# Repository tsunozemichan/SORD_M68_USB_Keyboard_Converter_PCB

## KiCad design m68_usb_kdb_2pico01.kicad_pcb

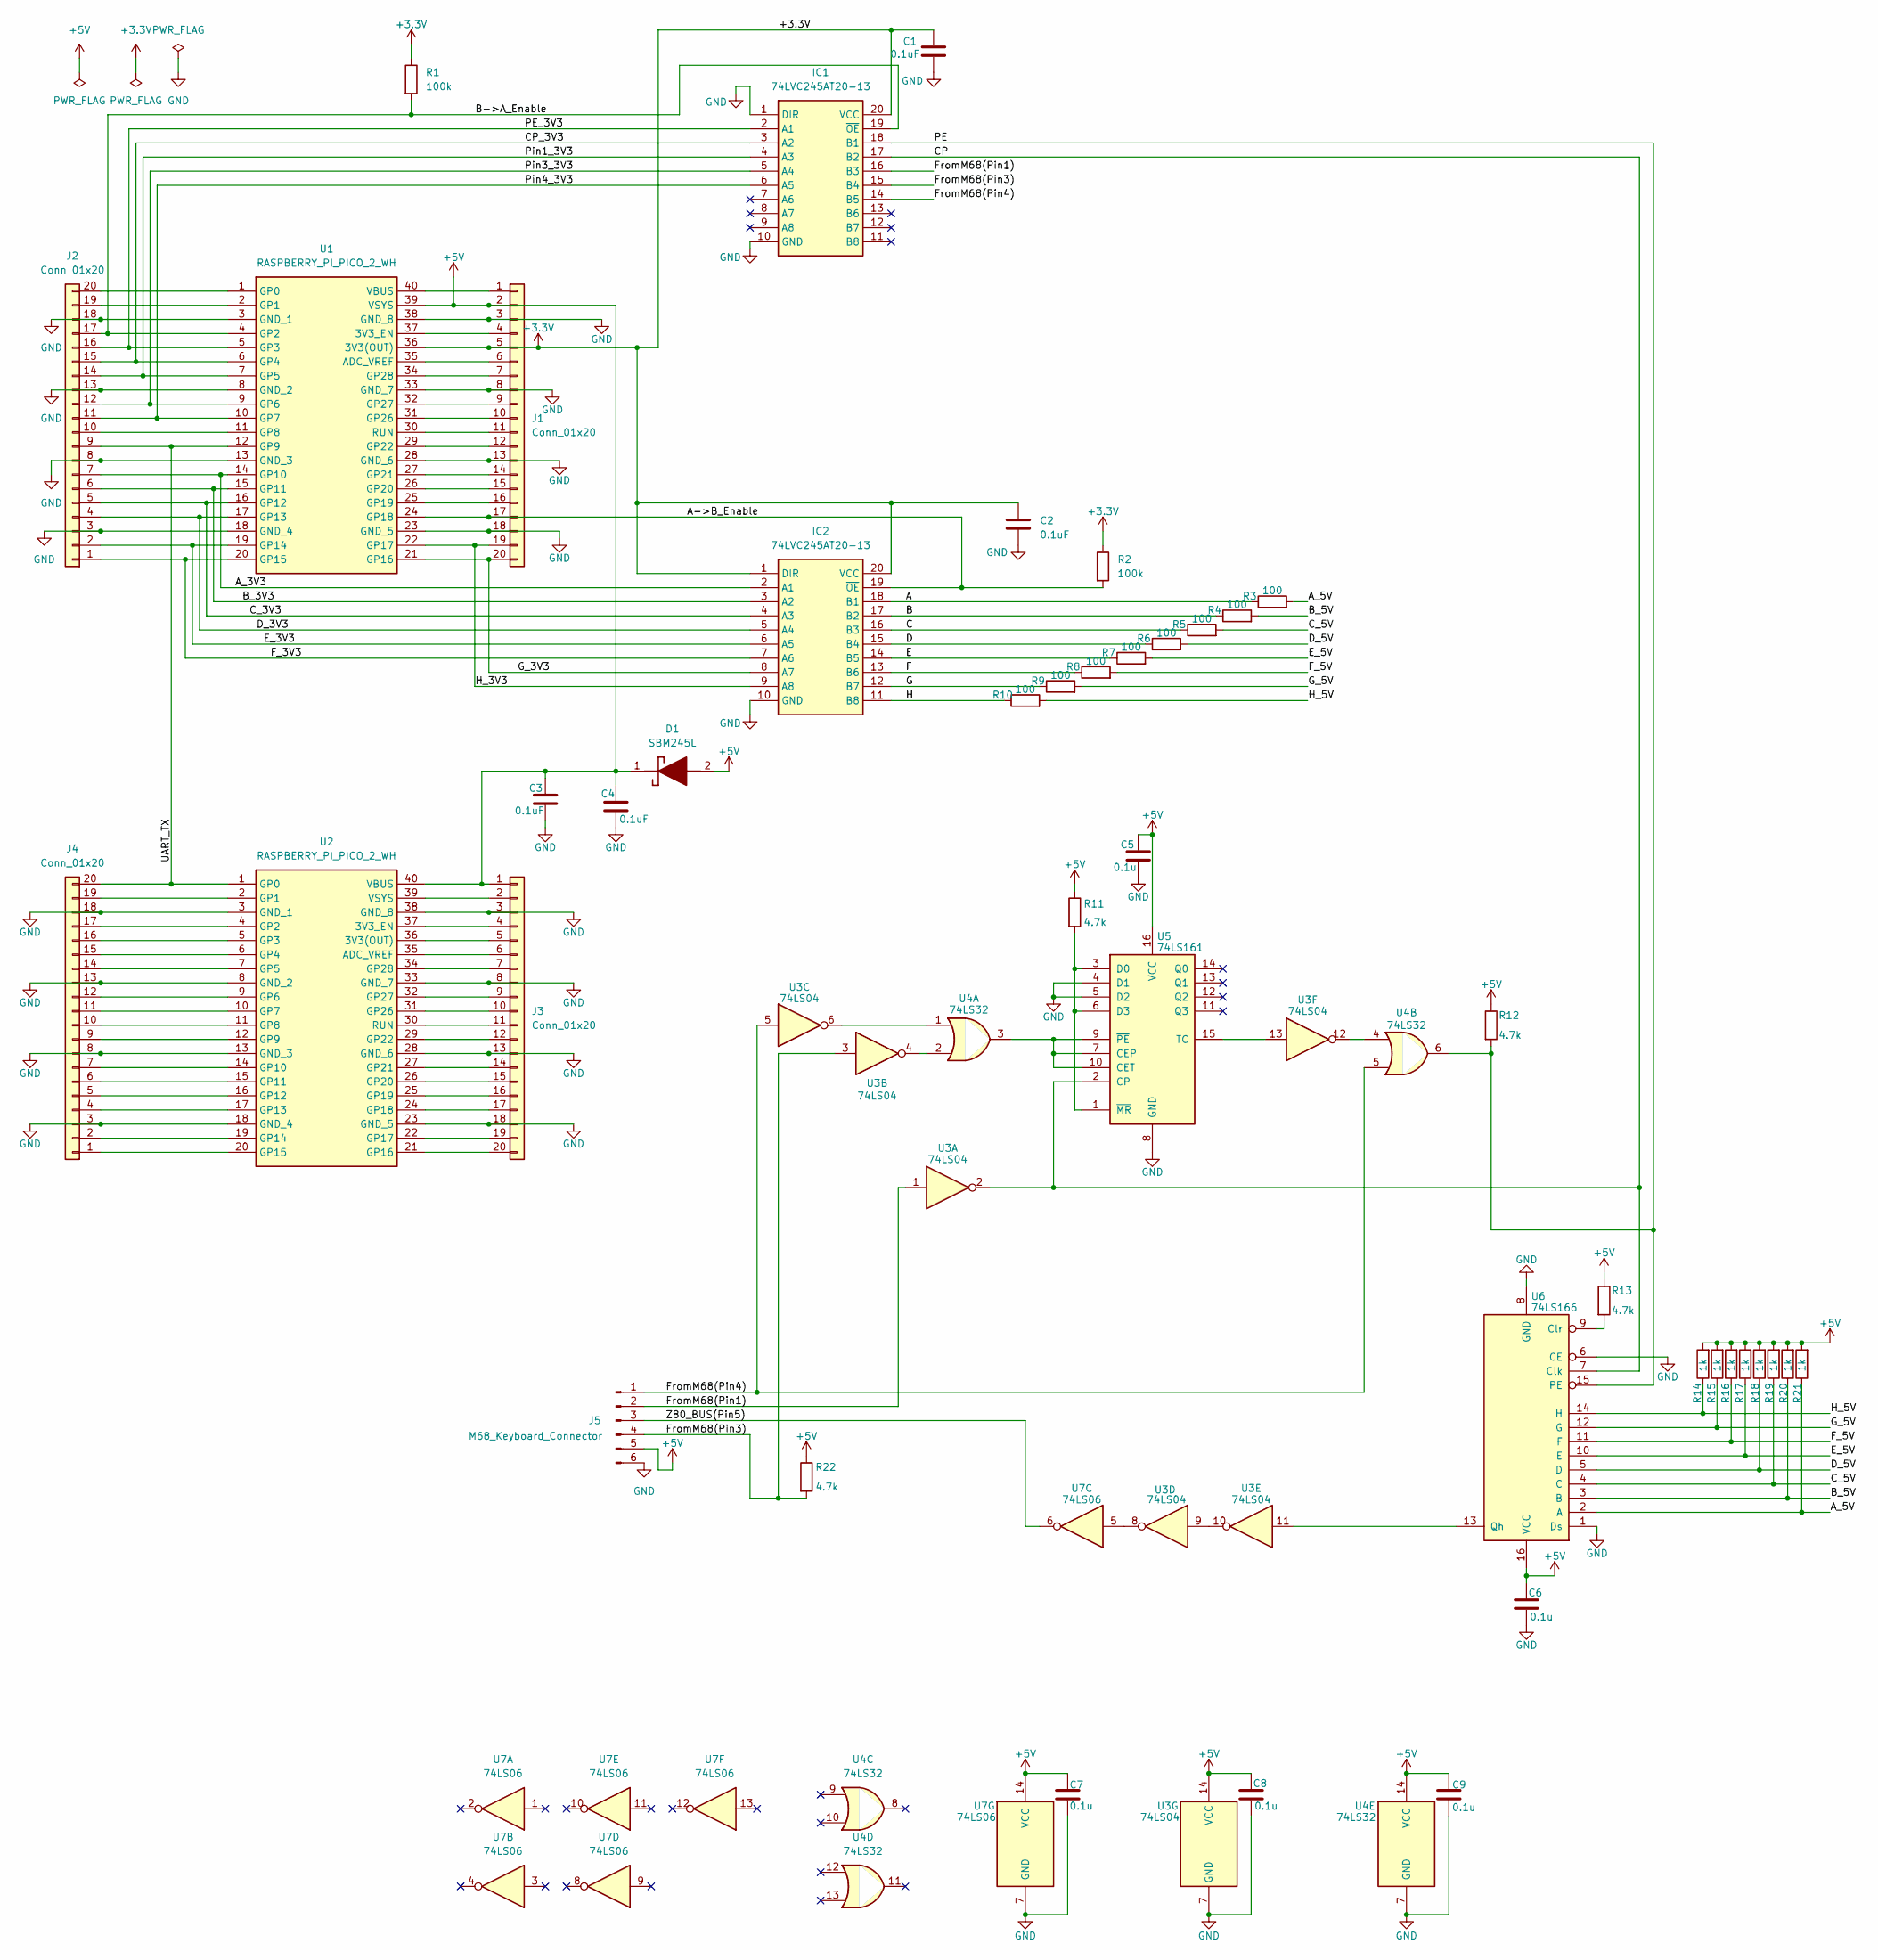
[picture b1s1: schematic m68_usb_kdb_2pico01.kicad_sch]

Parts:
C1, C2, C3, C4: 0.1uF; C_Disc_D3.0mm_W1.6mm_P2.50mm
C5, C6, C7, C8, C9: 0.1u; C_Disc_D5.0mm_W2.5mm_P2.50mm
D1: SBM245L; DIOAD1405W86L465D235; Manufacturer_Part_Number SBM245L
IC1, IC2: 74LVC245AT20-13; SOP65P640X120-20N; Manufacturer_Part_Number 74LVC245AT20-13; Mouser Part Number 621-74LVC245AT20-13
J1, J2, J3, J4: Conn_01x20; PinSocket_1x20_P2.54mm_Vertical
J5: M68_Keyboard_Connector; JST_XH_S6B-XH-A_1x06_P2.50mm_Horizontal
R1, R2: 100k; R_Axial_DIN0207_L6.3mm_D2.5mm_P10.16mm_Horizontal
R3, R4, R5, R6, R7, R8, R9, R10: 100; R_Axial_DIN0207_L6.3mm_D2.5mm_P10.16mm_Horizontal
R11, R12, R13, R22: 4.7k; R_Axial_DIN0207_L6.3mm_D2.5mm_P10.16mm_Horizontal
R14, R15, R16, R17, R18, R19, R20, R21: 1k; R_Axial_DIN0207_L6.3mm_D2.5mm_P10.16mm_Horizontal
U1, U2: RASPBERRY_PI_PICO_2_WH; RASPBERRYPIPICO2WH; Manufacturer_Part_Number RASPBERRY PI PICO 2 WH
U3: 74LS04; DIP-14_W7.62mm_Socket_LongPads
U4: 74LS32; DIP-14_W7.62mm_Socket_LongPads
U5: 74LS161; DIP-16_W7.62mm_Socket_LongPads
U6: 74LS166; DIP-16_W7.62mm_Socket_LongPads
U7: 74LS06; DIP-14_W7.62mm_Socket_LongPads

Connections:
+3.3V: C1.1, C2.1, IC1.20 (VCC), IC2.1 (DIR), IC2.20 (VCC), J1.5, R1.1, R2.1, U1.36 (3V3(OUT))
+5V: C3.1, C4.1, C5.1, C6.1, C7.1, C8.1, C9.1, D1.1 (K), D1.2 (A), J1.2, J3.1, J5.5, R11.1, R12.1, R13.1, R14.2, R15.2, R16.2, R17.2, R18.2, R19.2, R20.2, R21.2, R22.1, U1.39 (VSYS), U2.40 (VBUS), U3.14 (VCC), U4.14 (VCC), U5.16 (VCC), U6.16 (VCC), U7.14 (VCC)
/A: IC2.18 (B1), R3.1
/A->B_Enable: IC2.19 (~OE), J1.17, R2.2, U1.24 (GP18)
/A_3V3: IC2.2 (A1), J2.7, U1.14 (GP10)
/A_5V: R3.2, R21.1, U6.2 (A)
/B: IC2.17 (B2), R4.1
/B->A_Enable: IC1.19 (~OE), J2.17, R1.2, U1.4 (GP2)
/B_3V3: IC2.3 (A2), J2.6, U1.15 (GP11)
/B_5V: R4.2, R20.1, U6.3 (B)
/C: IC2.16 (B3), R5.1
/CP: IC1.17 (B2), U3.2, U5.2 (CP), U6.7 (Clk)
/CP_3V3: IC1.3 (A2), J2.15, U1.6 (GP4)
/C_3V3: IC2.4 (A3), J2.5, U1.16 (GP12)
/C_5V: R5.2, R19.1, U6.4 (C)
/D: IC2.15 (B4), R6.1
/D_3V3: IC2.5 (A4), J2.4, U1.17 (GP13)
/D_5V: R6.2, R18.1, U6.5 (D)
/E: IC2.14 (B5), R7.1
/E_3V3: IC2.6 (A5), J2.2, U1.19 (GP14)
/E_5V: R7.2, R17.1, U6.10 (E)
/F: IC2.13 (B6), R8.1
/F_3V3: IC2.7 (A6), J2.1, U1.20 (GP15)
/F_5V: R8.2, R16.1, U6.11 (F)
/FromM68(Pin1): IC1.16 (B3), J5.2, U3.1
/FromM68(Pin3): IC1.15 (B4), J5.4, R22.2, U3.3
/FromM68(Pin4): IC1.14 (B5), J5.1, U3.5, U4.5
/G: IC2.12 (B7), R9.1
/G_3V3: IC2.8 (A7), J1.20, U1.21 (GP16)
/G_5V: R9.2, R15.1, U6.12 (G)
/H: IC2.11 (B8), R10.1
/H_3V3: IC2.9 (A8), J1.19, U1.22 (GP17)
/H_5V: R10.2, R14.1, U6.14 (H)
/PE: IC1.18 (B1), R12.2, U4.6, U6.15 (PE)
/PE_3V3: IC1.2 (A1), J2.16, U1.5 (GP3)
/Pin1_3V3: IC1.4 (A3), J2.14, U1.7 (GP5)
/Pin3_3V3: IC1.5 (A4), J2.12, U1.9 (GP6)
/Pin4_3V3: IC1.6 (A5), J2.11, U1.10 (GP7)
/UART_TX: J2.9, J4.20, U1.12 (GP9), U2.1 (GP0)
/Z80_BUS(Pin5): J5.3, U7.6
GND: C1.2, C2.2, C3.2, C4.2, C5.2, C6.2, C7.2, C8.2, C9.2, IC1.1 (DIR), IC1.10 (GND), IC2.10 (GND), J1.3, J1.8, J1.13, J1.18, J2.3, J2.8, J2.13, J2.18, J3.3, J3.8, J3.13, J3.18, J4.3, J4.8, J4.13, J4.18, J5.6, U1.3 (GND_1), U1.8 (GND_2), U1.13 (GND_3), U1.18 (GND_4), U1.23 (GND_5), U1.28 (GND_6), U1.33 (GND_7), U1.38 (GND_8), U2.3 (GND_1), U2.8 (GND_2), U2.13 (GND_3), U2.18 (GND_4), U2.23 (GND_5), U2.28 (GND_6), U2.33 (GND_7), U2.38 (GND_8), U3.7 (GND), U4.7 (GND), U5.4 (D1), U5.5 (D2), U5.8 (GND), U6.1 (Ds), U6.6 (CE), U6.8 (GND), U7.7 (GND)
unnamed: J1.1, U1.40 (VBUS)
unnamed: J1.4, U1.37 (3V3_EN)
unnamed: J1.6, U1.35 (ADC_VREF)
unnamed: J1.7, U1.34 (GP28)
unnamed: J1.9, U1.32 (GP27)
unnamed: J1.10, U1.31 (GP26)
unnamed: J1.11, U1.30 (RUN)
unnamed: J1.12, U1.29 (GP22)
unnamed: J1.14, U1.27 (GP21)
unnamed: J1.15, U1.26 (GP20)
unnamed: J1.16, U1.25 (GP19)
unnamed: J2.10, U1.11 (GP8)
unnamed: J2.19, U1.2 (GP1)
unnamed: J2.20, U1.1 (GP0)
unnamed: J3.2, U2.39 (VSYS)
unnamed: J3.4, U2.37 (3V3_EN)
unnamed: J3.5, U2.36 (3V3(OUT))
unnamed: J3.6, U2.35 (ADC_VREF)
unnamed: J3.7, U2.34 (GP28)
unnamed: J3.9, U2.32 (GP27)
unnamed: J3.10, U2.31 (GP26)
unnamed: J3.11, U2.30 (RUN)
unnamed: J3.12, U2.29 (GP22)
unnamed: J3.14, U2.27 (GP21)
unnamed: J3.15, U2.26 (GP20)
unnamed: J3.16, U2.25 (GP19)
unnamed: J3.17, U2.24 (GP18)
unnamed: J3.19, U2.22 (GP17)
unnamed: J3.20, U2.21 (GP16)
unnamed: J4.1, U2.20 (GP15)
unnamed: J4.2, U2.19 (GP14)
unnamed: J4.4, U2.17 (GP13)
unnamed: J4.5, U2.16 (GP12)
unnamed: J4.6, U2.15 (GP11)
unnamed: J4.7, U2.14 (GP10)
unnamed: J4.9, U2.12 (GP9)
unnamed: J4.10, U2.11 (GP8)
unnamed: J4.11, U2.10 (GP7)
unnamed: J4.12, U2.9 (GP6)
unnamed: J4.14, U2.7 (GP5)
unnamed: J4.15, U2.6 (GP4)
unnamed: J4.16, U2.5 (GP3)
unnamed: J4.17, U2.4 (GP2)
unnamed: J4.19, U2.2 (GP1)
unnamed: U3.4, U4.2
unnamed: U3.6, U4.1
unnamed: U3.8, U7.5
unnamed: U3.9, U3.10
unnamed: U3.12, U4.4
unnamed: U4.3, U5.7 (CEP), U5.9 (~PE), U5.10 (CET)
unnamed: R11.2, U5.1 (~MR), U5.3 (D0), U5.6 (D3)
unnamed: U3.13, U5.15 (TC)
unnamed: R13.2, U6.9 (Clr)
unnamed: U3.11, U6.13 (Qh)

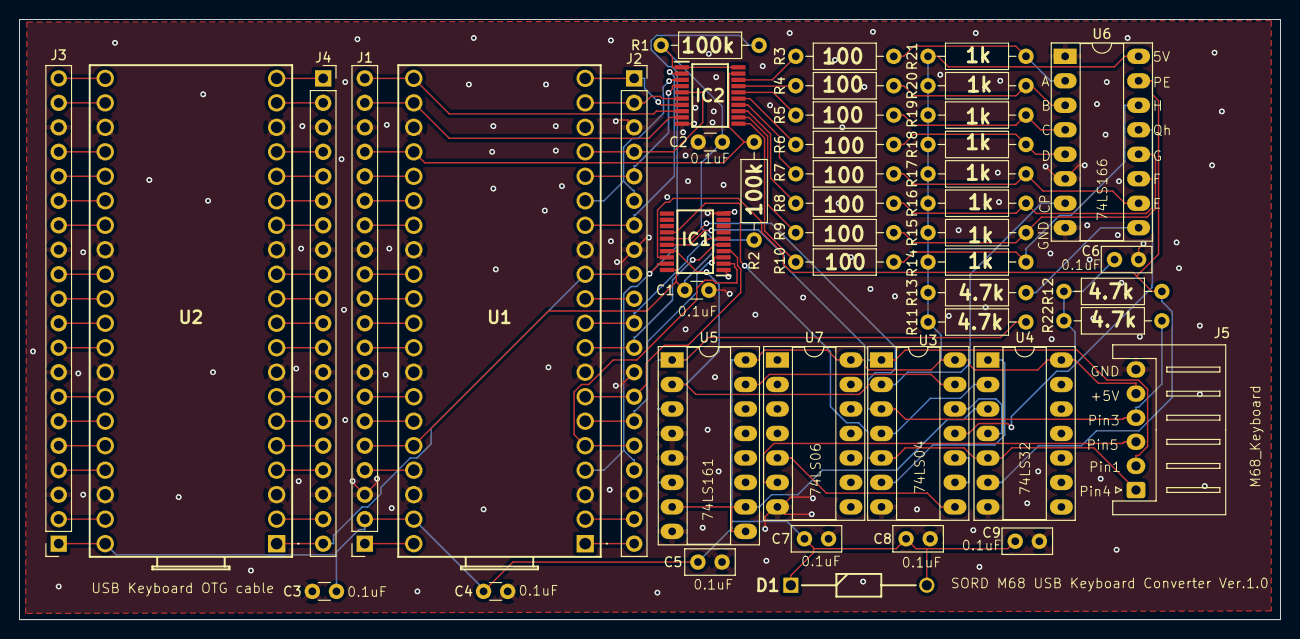
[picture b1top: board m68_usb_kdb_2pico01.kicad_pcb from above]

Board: 2 copper layers, 130.8 x 62.2 mm, 46 parts (0 on the bottom side), 95 nets.

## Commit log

2025-10-30 add files
